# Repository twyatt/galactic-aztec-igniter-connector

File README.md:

# About

Custom board used to convert igniter ethernet plugs to 2-position terminal blocks for the [Galactic Aztec] rocket. The board was designed to interface with the [Galactic Aztec Raspberry Pi Add-on: Igniter] board.

Custom EagleCAD parts on this board can be found in the [SDSU Rocket Eagle Libraries].

## Wiring
The ethernet ports adhere to the following [T-568B] wiring configurations:

### Igniter
| Pin | Color        | Function       |
|:---:|:------------:|:--------------:|
| 1   | Orange/White | Supply Voltage |
| 2   | Orange       | Ground         |
| 3   | Green/White  | Supply Voltage |
| 4   | Blue         | Ground         |
| 5   | Blue/White   | Supply Voltage |
| 6   | Green        | Ground         |
| 7   | Brown/White  | Supply Voltage |
| 8   | Brown        | Ground         |

### Break Wire
| Pin | Color        | Function       |
|:---:|:------------:|:--------------:|
| 1   | Orange/White | 3.3V           |
| 2   | Orange       | Signal         |
| 3   | Green/White  | 3.3V           |
| 4   | Blue         | Signal         |
| 5   | Blue/White   | 3.3V           |
| 6   | Green        | Signal         |
| 7   | Brown/White  | 3.3V           |
| 8   | Brown        | Signal         |

## Launch
For the [Galactic Aztec April 18th, 2015 launch], a strand of solder was screwed into one side of the terminal block labeled "Break" then run thru the igniter and back to the other side of the "Break" terminal block. The "Break" terminal block does not have a polarity and simply opens or closes the connection between 3.3V and Signal.

# Bill of Materials
| Qty | Description                               | Part Number       | Vendor   |
|:---:|-------------------------------------------|------------------:|----------|
| 1   | Jack RJ45 CAT5/CAT5e                      | [380-1046-ND]     | DigiKey  |
| 1   | LED Red Vf=1.8V If=2mA 0603               | [475-1195-2-ND]   | DigiKey  |
| 1   | Resistor 12kΩ 1/4W 1% 0603                | [RHM12.0KADCT-ND] | DigiKey  |
| 3   | Terminal Block 0.2" Pitch Plug            | [A98223-ND]       | DigiKey  |
| 3   | Terminal Block 0.2" Pitch Socket          | [A98235-ND]       | DigiKey  |

[Galactic Aztec]: http://rocket.sdsu.edu/rockets
[Galactic Aztec Raspberry Pi Add-on: Igniter]: https://github.com/twyatt/galactic-aztec-rpi-addon-igniter
[SDSU Rocket Eagle Libraries]: https://github.com/twyatt/SDSURocket-Eagle-Libraries
[T-568B]: https://en.wikipedia.org/wiki/TIA/EIA-568#Wiring
[Galactic Aztec April 18th, 2015 launch]: https://github.com/twyatt/galactic-aztec-launch-data
[380-1046-ND]: http://www.digikey.com/product-detail/en/SS-7188-NF/380-1046-ND/388308
[475-1195-2-ND]: http://www.digikey.com/product-detail/en/LS%20L29K-H1J2-1-Z/475-1195-1-ND/810356
[RHM12.0KADCT-ND]: http://www.digikey.com/product-detail/en/ESR03EZPF1202/RHM12.0KADCT-ND/1983756
[A98223-ND]: http://www.digikey.com/product-detail/en/796634-2/A98223-ND/1827082
[A98235-ND]: http://www.digikey.com/product-detail/en/796638-2/A98235-ND/1827094

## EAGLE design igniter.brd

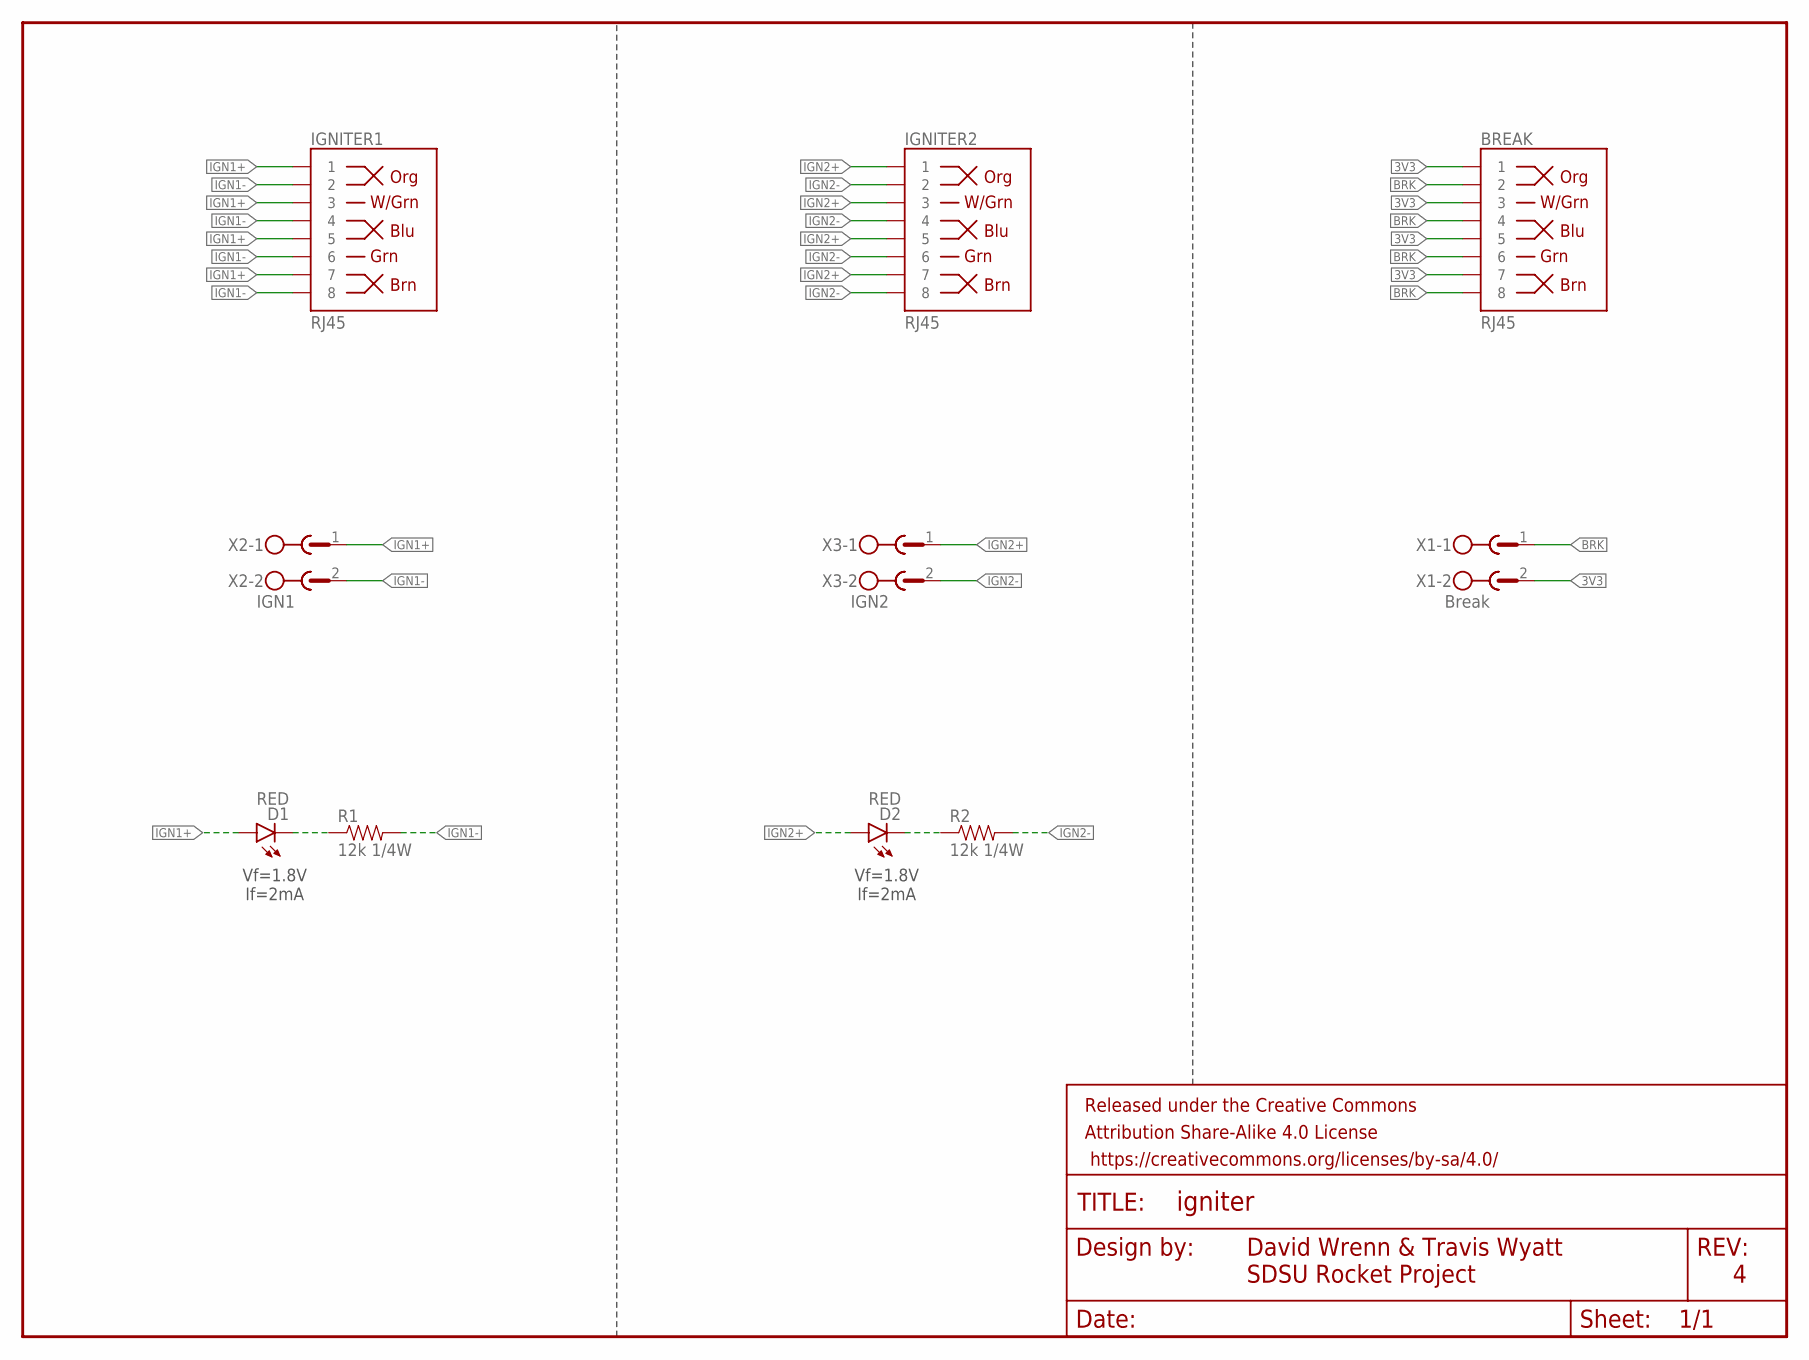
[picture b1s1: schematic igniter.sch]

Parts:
BREAK: RJ45; RJ45-8
D1, D2: RED; LED-0603
FRAME1: FRAME-LETTER; CREATIVE_COMMONS
IGNITER1, IGNITER2: RJ45; RJ45-8
R1, R2: 12k 1/4W; 0603-RES
X1: Break; MSTBA2
X2: IGN1; MSTBA2
X3: IGN2; MSTBA2

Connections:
3V3: BREAK.1, BREAK.3, BREAK.5, BREAK.7, X1.2
BRK: BREAK.2, BREAK.4, BREAK.6, BREAK.8, X1.1
IGN1+: D1.A, IGNITER1.1, IGNITER1.3, IGNITER1.5, IGNITER1.7, X2.1
IGN1-: IGNITER1.2, IGNITER1.4, IGNITER1.6, IGNITER1.8, R1.2, X2.2
IGN2+: D2.A, IGNITER2.1, IGNITER2.3, IGNITER2.5, IGNITER2.7, X3.1
IGN2-: IGNITER2.2, IGNITER2.4, IGNITER2.6, IGNITER2.8, R2.2, X3.2
unnamed: D1.C, R1.1
unnamed: D2.C, R2.1

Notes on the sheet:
David Wrenn & Travis Wyatt
SDSU Rocket Project
Vf=1.8V If=2mA

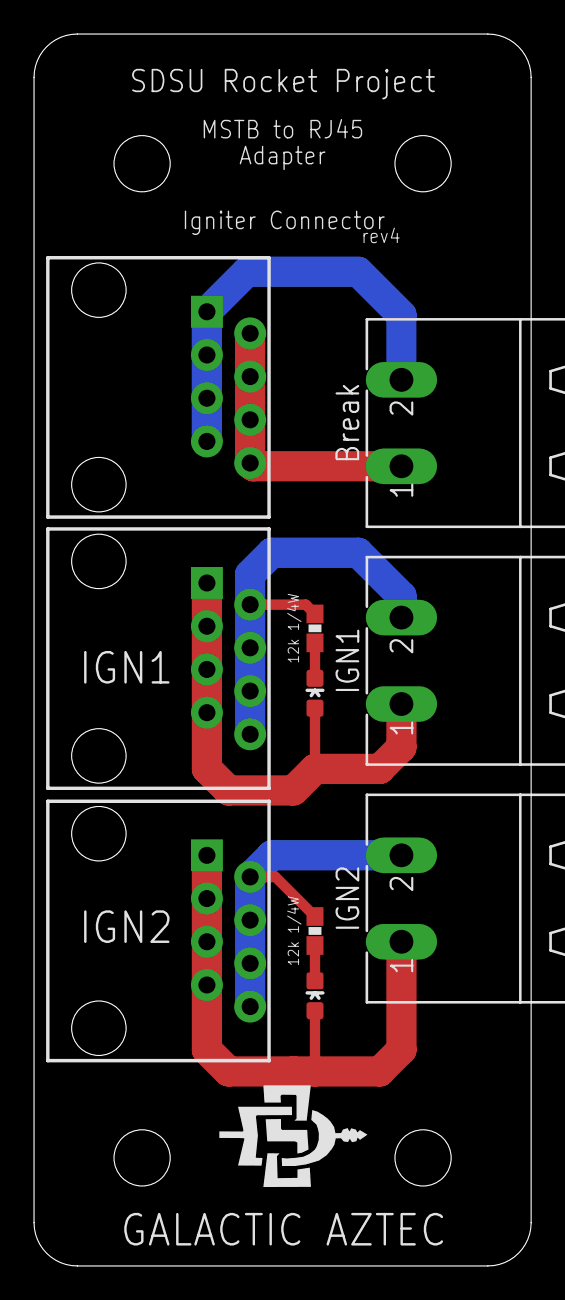
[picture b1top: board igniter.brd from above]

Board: 2 copper layers, 29.2 x 72.4 mm, 15 parts (0 on the bottom side), 8 nets.

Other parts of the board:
U$1, U$2, U$3, U$4: STAND-OFF

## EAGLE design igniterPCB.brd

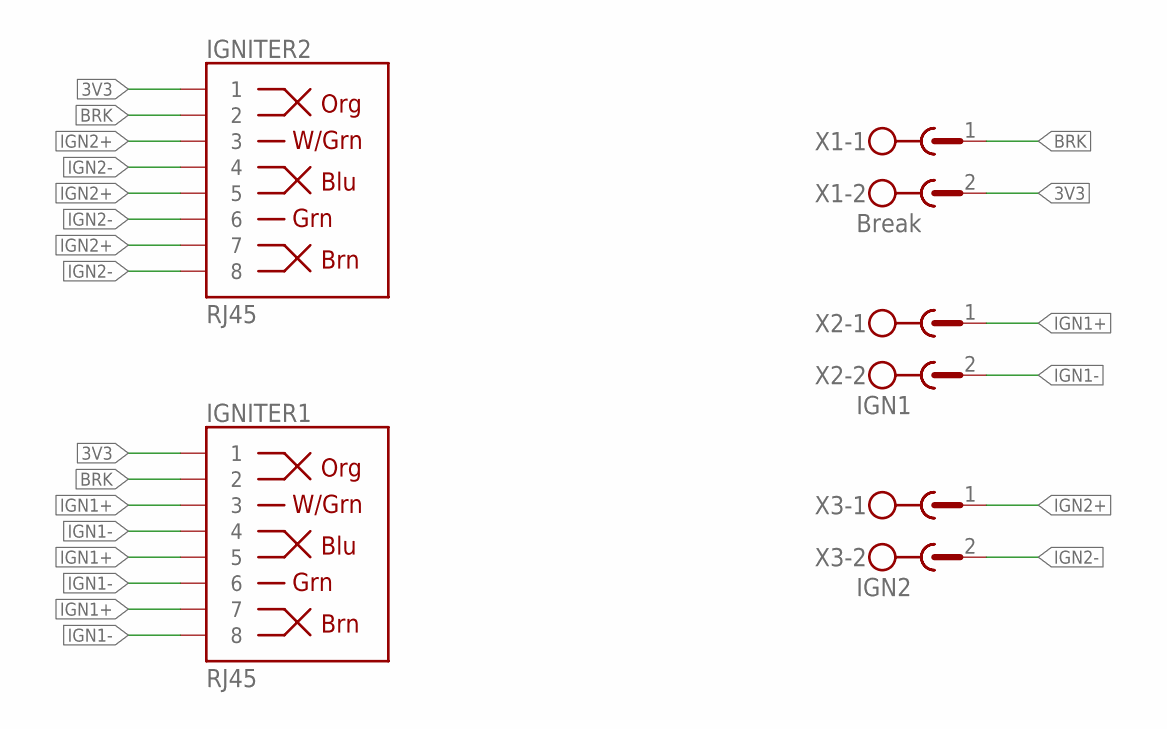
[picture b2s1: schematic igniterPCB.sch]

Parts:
IGNITER1, IGNITER2: RJ45; RJ45-8
X1: Break; MSTBA2
X2: IGN1; MSTBA2
X3: IGN2; MSTBA2

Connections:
3V3: IGNITER1.1, IGNITER2.1, X1.2
BRK: IGNITER1.2, IGNITER2.2, X1.1
IGN1+: IGNITER1.3, IGNITER1.5, IGNITER1.7, X2.1
IGN1-: IGNITER1.4, IGNITER1.6, IGNITER1.8, X2.2
IGN2+: IGNITER2.3, IGNITER2.5, IGNITER2.7, X3.1
IGN2-: IGNITER2.4, IGNITER2.6, IGNITER2.8, X3.2

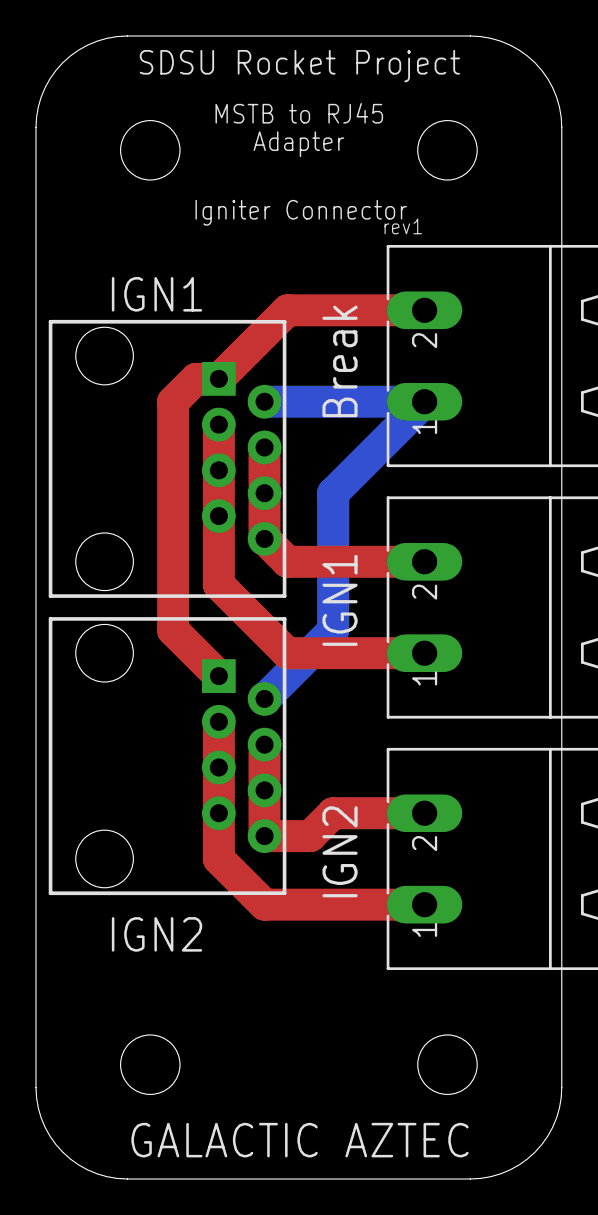
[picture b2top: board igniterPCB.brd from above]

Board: 2 copper layers, 29.2 x 63.5 mm, 9 parts (0 on the bottom side), 6 nets.

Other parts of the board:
U$1, U$2, U$3, U$4: STAND-OFF

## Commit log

2015-07-28 Initial commit.
2015-07-28 Added ignition status LEDs. Separated break wire from ignition wires. Added SDSU logo.
2015-07-29 Updated to use more efficient LEDs. Decreased SMD resistor size to 0603.

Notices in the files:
parts and their libraries:
SparkFun-Connectors: Licensing: Creative Commons ShareAlike 4.0 International - https://creativecommons.org/licenses/by-sa/4.0
SparkFun-Aesthetics: Released under the Creative Commons Attribution Share-Alike 4.0 License
SparkFun-Aesthetics: https://creativecommons.org/licenses/by-sa/4.0
